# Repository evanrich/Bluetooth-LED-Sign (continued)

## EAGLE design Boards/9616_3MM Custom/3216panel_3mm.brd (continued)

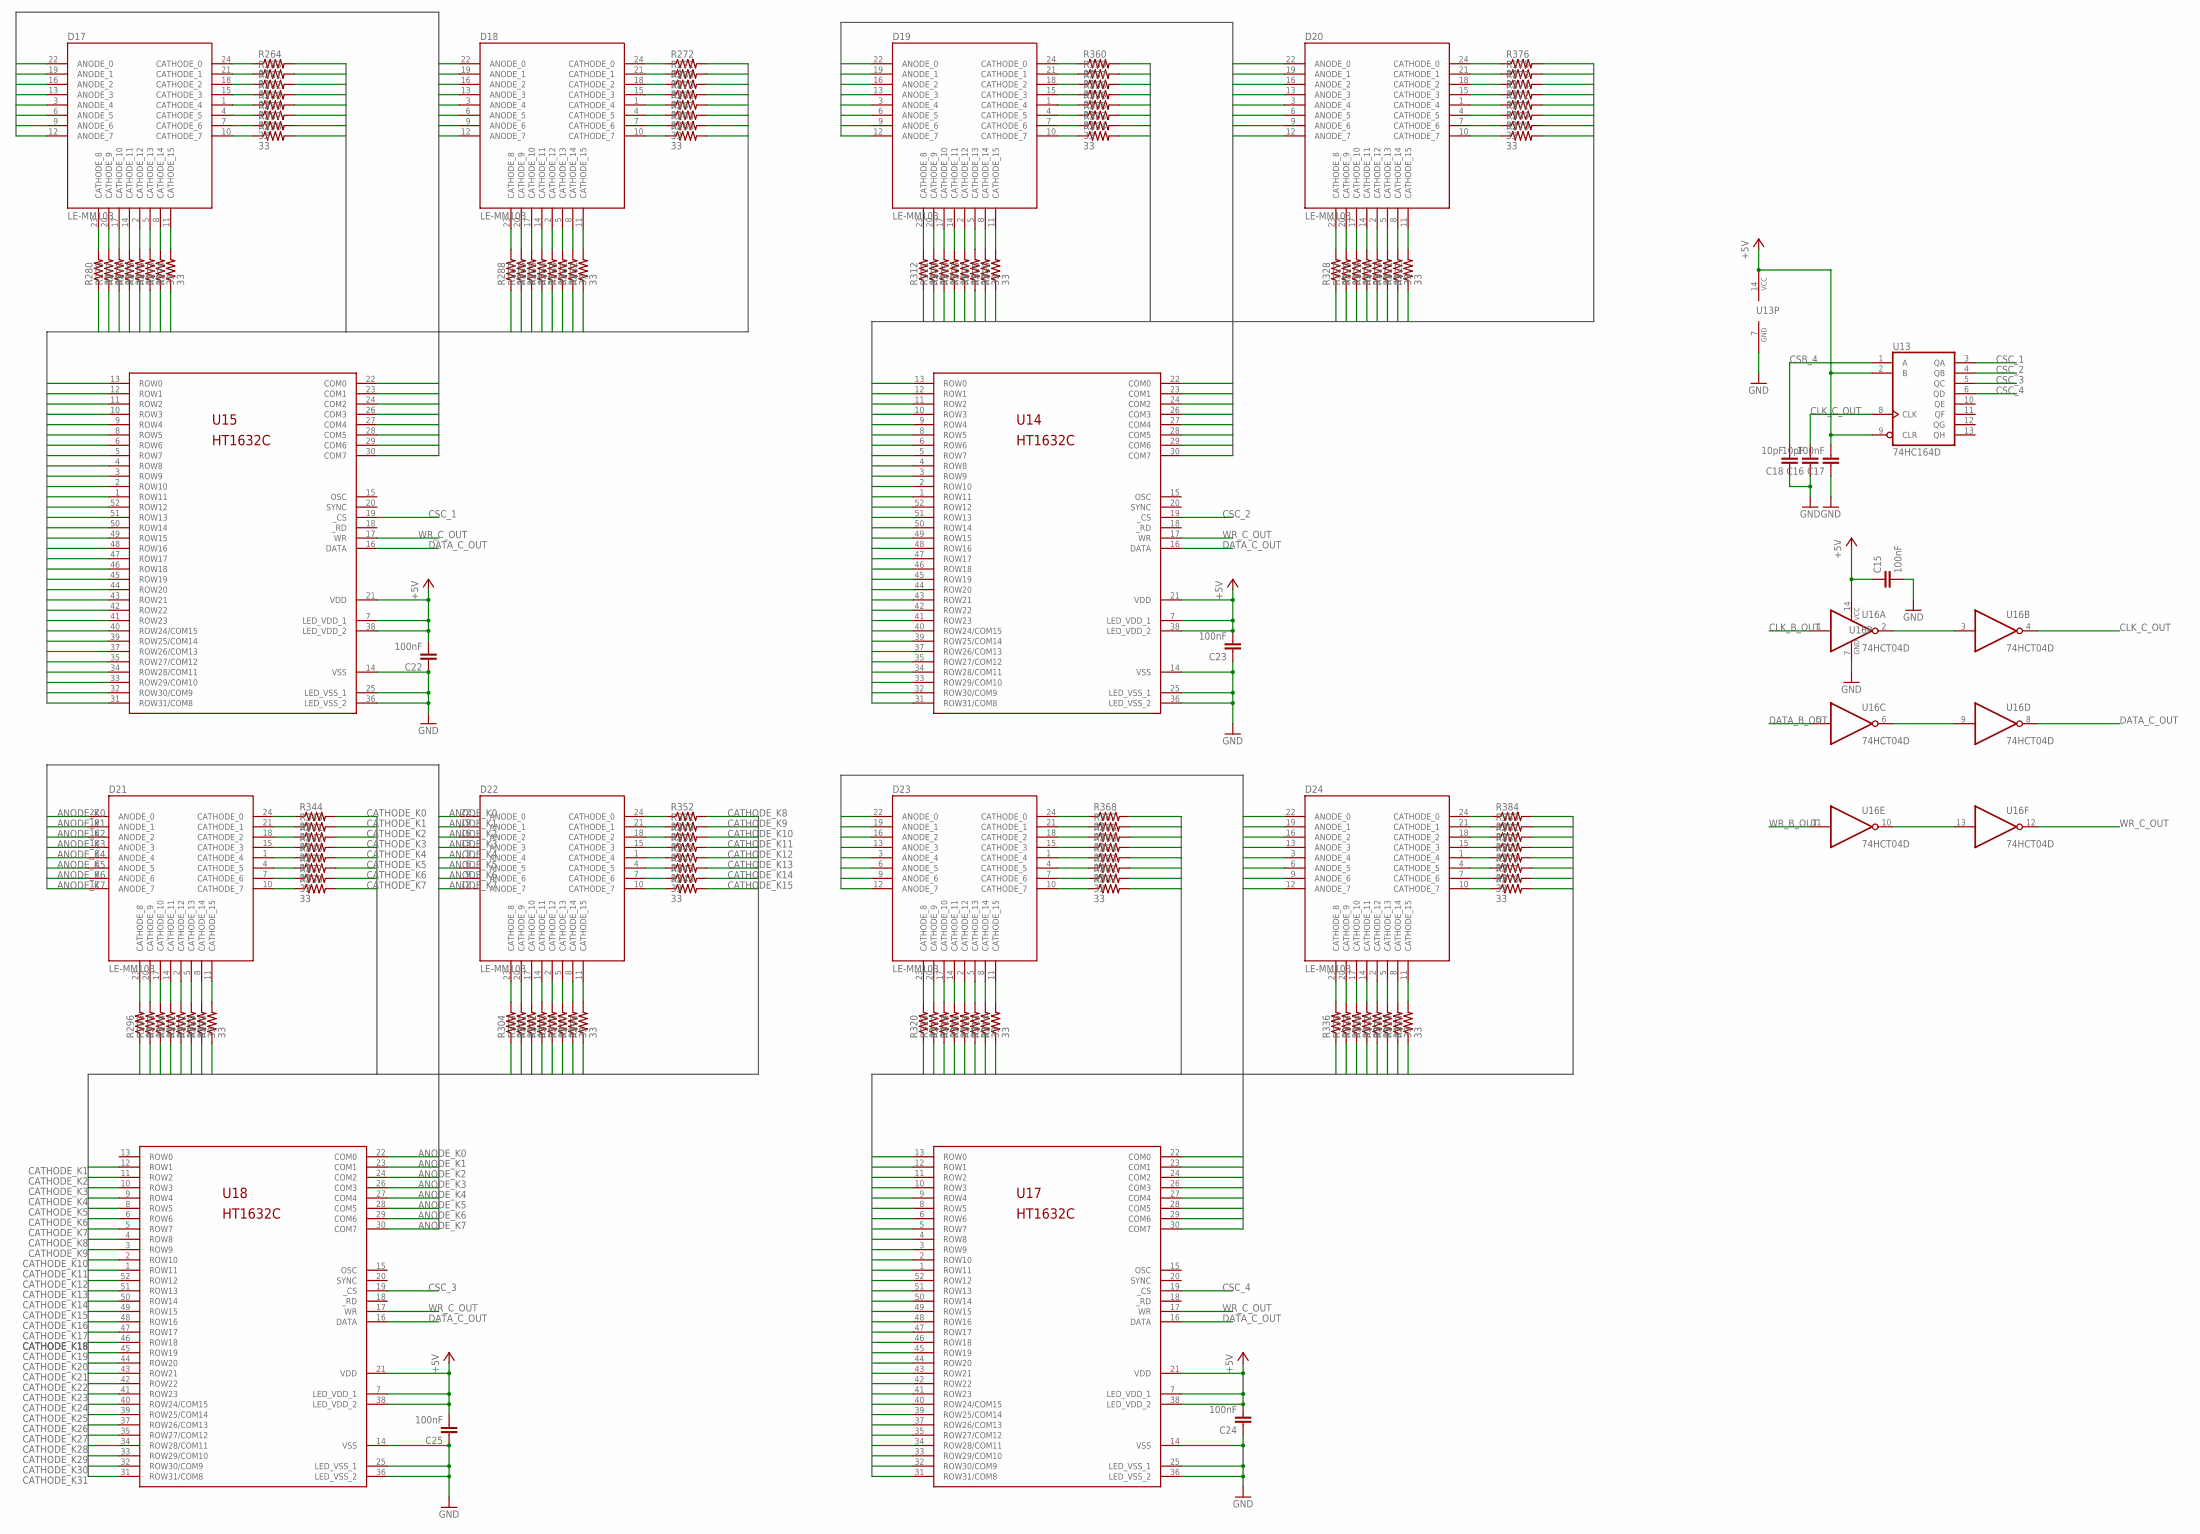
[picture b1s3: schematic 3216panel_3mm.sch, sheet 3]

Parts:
C15, C17, C22, C23, C24, C25: 100nF; 0805
C16, C18: 10pF; 0805
D17, D18, D19, D20, D21, D22, D23, D24: LE-MM103; 8X8_3MM_LED_MATRIX
R257, R258, R259, R260, R261, R262, R263, R264, R265, R266, R267, R268, R269, R270, R271, R272, R273, R274, R275, R276, R277, R278, R279, R280, R281, R282, R283, R284, R285, R286, R287, R288, R289, R290, R291, R292, R293, R294, R295, R296, R297, R298, R299, R300, R301, R302, R303, R304, R305, R306, R307, R308, R309, R310, R311, R312, R313, R314, R315, R316, R317, R318, R319, R320, R321, R322, R323, R324, R325, R326, R327, R328, R329, R330, R331, R332, R333, R334, R335, R336, R337, R338, R339, R340, R341, R342, R343, R344, R345, R346, R347, R348, R349, R350, R351, R352, R353, R354, R355, R356, R357, R358, R359, R360, R361, R362, R363, R364, R365, R366, R367, R368, R369, R370, R371, R372, R373, R374, R375, R376, R377, R378, R379, R380, R381, R382, R383, R384: 33; 0805
U13: 74HC164D; SO14
U14, U15, U17, U18: HT1632C; QFP52
U16: 74HCT04D; SO14

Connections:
+5V: C15.1, C17.2, C22.2, C23.2, C24.2, C25.2, U13.2 (B), U13.9 (CLR), U13.14 (VCC), U14.7 (LED_VDD_1), U14.21 (VDD), U14.38 (LED_VDD_2), U15.7 (LED_VDD_1), U15.21 (VDD), U15.38 (LED_VDD_2), U16.14 (VCC), U17.7 (LED_VDD_1), U17.21 (VDD), U17.38 (LED_VDD_2), U18.7 (LED_VDD_1), U18.21 (VDD), U18.38 (LED_VDD_2); also elsewhere on the board
ANODE_I0: D17.22 (ANODE_0), D18.22 (ANODE_0), U15.22 (COM0)
ANODE_I1: D17.19 (ANODE_1), D18.19 (ANODE_1), U15.23 (COM1)
ANODE_I2: D17.16 (ANODE_2), D18.16 (ANODE_2), U15.24 (COM2)
ANODE_I3: D17.13 (ANODE_3), D18.13 (ANODE_3), U15.26 (COM3)
ANODE_I4: D17.3 (ANODE_4), D18.3 (ANODE_4), U15.27 (COM4)
ANODE_I5: D17.6 (ANODE_5), D18.6 (ANODE_5), U15.28 (COM5)
ANODE_I6: D17.9 (ANODE_6), D18.9 (ANODE_6), U15.29 (COM6)
ANODE_I7: D17.12 (ANODE_7), D18.12 (ANODE_7), U15.30 (COM7)
ANODE_J0: D19.22 (ANODE_0), D20.22 (ANODE_0), U14.22 (COM0)
ANODE_J1: D19.19 (ANODE_1), D20.19 (ANODE_1), U14.23 (COM1)
ANODE_J2: D19.16 (ANODE_2), D20.16 (ANODE_2), U14.24 (COM2)
ANODE_J3: D19.13 (ANODE_3), D20.13 (ANODE_3), U14.26 (COM3)
ANODE_J4: D19.3 (ANODE_4), D20.3 (ANODE_4), U14.27 (COM4)
ANODE_J5: D19.6 (ANODE_5), D20.6 (ANODE_5), U14.28 (COM5)
ANODE_J6: D19.9 (ANODE_6), D20.9 (ANODE_6), U14.29 (COM6)
ANODE_J7: D19.12 (ANODE_7), D20.12 (ANODE_7), U14.30 (COM7)
ANODE_K0: D21.22 (ANODE_0), D22.22 (ANODE_0), U18.22 (COM0)
ANODE_K1: D21.19 (ANODE_1), D22.19 (ANODE_1), U18.23 (COM1)
ANODE_K2: D21.16 (ANODE_2), D22.16 (ANODE_2), U18.24 (COM2)
ANODE_K3: D21.13 (ANODE_3), D22.13 (ANODE_3), U18.26 (COM3)
ANODE_K4: D21.3 (ANODE_4), D22.3 (ANODE_4), U18.27 (COM4)
ANODE_K5: D21.6 (ANODE_5), D22.6 (ANODE_5), U18.28 (COM5)
ANODE_K6: D21.9 (ANODE_6), D22.9 (ANODE_6), U18.29 (COM6)
ANODE_K7: D21.12 (ANODE_7), D22.12 (ANODE_7), U18.30 (COM7)
ANODE_L0: D23.22 (ANODE_0), D24.22 (ANODE_0), U17.22 (COM0)
ANODE_L1: D23.19 (ANODE_1), D24.19 (ANODE_1), U17.23 (COM1)
ANODE_L2: D23.16 (ANODE_2), D24.16 (ANODE_2), U17.24 (COM2)
ANODE_L3: D23.13 (ANODE_3), D24.13 (ANODE_3), U17.26 (COM3)
ANODE_L4: D23.3 (ANODE_4), D24.3 (ANODE_4), U17.27 (COM4)
ANODE_L5: D23.6 (ANODE_5), D24.6 (ANODE_5), U17.28 (COM5)
ANODE_L6: D23.9 (ANODE_6), D24.9 (ANODE_6), U17.29 (COM6)
ANODE_L7: D23.12 (ANODE_7), D24.12 (ANODE_7), U17.30 (COM7)
CATHODE_I0: R264.2, U15.13 (ROW0)
CATHODE_I1: R263.2, U15.12 (ROW1)
CATHODE_I2: R261.2, U15.11 (ROW2)
CATHODE_I3: R262.2, U15.10 (ROW3)
CATHODE_I4: R260.2, U15.9 (ROW4)
CATHODE_I5: R259.2, U15.8 (ROW5)
CATHODE_I6: R257.2, U15.6 (ROW6)
CATHODE_I7: R258.2, U15.5 (ROW7)
CATHODE_I8: R272.2, U15.4 (ROW8)
CATHODE_I9: R271.2, U15.3 (ROW9)
CATHODE_I10: R269.2, U15.2 (ROW10)
CATHODE_I11: R270.2, U15.1 (ROW11)
CATHODE_I12: R268.2, U15.52 (ROW12)
CATHODE_I13: R267.2, U15.51 (ROW13)
CATHODE_I14: R265.2, U15.50 (ROW14)
CATHODE_I15: R266.2, U15.49 (ROW15)
CATHODE_I16: R280.1, U15.48 (ROW16)
CATHODE_I17: R279.1, U15.47 (ROW17)
CATHODE_I18: R277.1, U15.46 (ROW18)
CATHODE_I19: R278.1, U15.45 (ROW19)
CATHODE_I20: R276.1, U15.44 (ROW20)
CATHODE_I21: R275.1, U15.43 (ROW21)
CATHODE_I22: R273.1, U15.42 (ROW22)
CATHODE_I23: R274.1, U15.41 (ROW23)
CATHODE_I24: R288.1, U15.40 (ROW24/COM15)
CATHODE_I25: R287.1, U15.39 (ROW25/COM14)
CATHODE_I26: R285.1, U15.37 (ROW26/COM13)
CATHODE_I27: R286.1, U15.35 (ROW27/COM12)
CATHODE_I28: R284.1, U15.34 (ROW28/COM11)
CATHODE_I29: R283.1, U15.33 (ROW29/COM10)
CATHODE_I30: R281.1, U15.32 (ROW30/COM9)
CATHODE_I31: R282.1, U15.31 (ROW31/COM8)
CATHODE_J0: R360.2, U14.13 (ROW0)
CATHODE_J1: R359.2, U14.12 (ROW1)
CATHODE_J2: R357.2, U14.11 (ROW2)
CATHODE_J3: R358.2, U14.10 (ROW3)
CATHODE_J4: R356.2, U14.9 (ROW4)
CATHODE_J5: R355.2, U14.8 (ROW5)
CATHODE_J6: R353.2, U14.6 (ROW6)
CATHODE_J7: R354.2, U14.5 (ROW7)
CATHODE_J8: R376.2, U14.4 (ROW8)
CATHODE_J9: R375.2, U14.3 (ROW9)
CATHODE_J10: R373.2, U14.2 (ROW10)
CATHODE_J11: R374.2, U14.1 (ROW11)
CATHODE_J12: R372.2, U14.52 (ROW12)
CATHODE_J13: R371.2, U14.51 (ROW13)
CATHODE_J14: R369.2, U14.50 (ROW14)
CATHODE_J15: R370.2, U14.49 (ROW15)
CATHODE_J16: R312.1, U14.48 (ROW16)
CATHODE_J17: R311.1, U14.47 (ROW17)
CATHODE_J18: R309.1, U14.46 (ROW18)
CATHODE_J19: R310.1, U14.45 (ROW19)
CATHODE_J20: R308.1, U14.44 (ROW20)
CATHODE_J21: R307.1, U14.43 (ROW21)
CATHODE_J22: R305.1, U14.42 (ROW22)
CATHODE_J23: R306.1, U14.41 (ROW23)
CATHODE_J24: R328.1, U14.40 (ROW24/COM15)
CATHODE_J25: R327.1, U14.39 (ROW25/COM14)
CATHODE_J26: R325.1, U14.37 (ROW26/COM13)
CATHODE_J27: R326.1, U14.35 (ROW27/COM12)
CATHODE_J28: R324.1, U14.34 (ROW28/COM11)
CATHODE_J29: R323.1, U14.33 (ROW29/COM10)
CATHODE_J30: R321.1, U14.32 (ROW30/COM9)
CATHODE_J31: R322.1, U14.31 (ROW31/COM8)
CATHODE_K0: R344.2
CATHODE_K1: R343.2, U18.12 (ROW1)
CATHODE_K2: R341.2, U18.11 (ROW2)
CATHODE_K3: R342.2, U18.10 (ROW3)
CATHODE_K4: R340.2, U18.9 (ROW4)
CATHODE_K5: R339.2, U18.8 (ROW5)
CATHODE_K6: R337.2, U18.6 (ROW6)
CATHODE_K7: R338.2, U18.5 (ROW7)
CATHODE_K8: R352.2, U18.4 (ROW8)
CATHODE_K9: R351.2, U18.3 (ROW9)
CATHODE_K10: R349.2, U18.2 (ROW10)
CATHODE_K11: R350.2, U18.1 (ROW11)
CATHODE_K12: R348.2, U18.52 (ROW12)
CATHODE_K13: R347.2, U18.51 (ROW13)
CATHODE_K14: R345.2, U18.50 (ROW14)
CATHODE_K15: R346.2, U18.49 (ROW15)
CATHODE_K16: R296.1, U18.48 (ROW16)
CATHODE_K17: R295.1, U18.47 (ROW17)
CATHODE_K18: R293.1, U18.46 (ROW18)
CATHODE_K19: R294.1, U18.45 (ROW19)
CATHODE_K20: R292.1, U18.44 (ROW20)
CATHODE_K21: R291.1, U18.43 (ROW21)
CATHODE_K22: R289.1, U18.42 (ROW22)
CATHODE_K23: R290.1, U18.41 (ROW23)
CATHODE_K24: R304.1, U18.40 (ROW24/COM15)
CATHODE_K25: R303.1, U18.39 (ROW25/COM14)
CATHODE_K26: R301.1, U18.37 (ROW26/COM13)
CATHODE_K27: R302.1, U18.35 (ROW27/COM12)
CATHODE_K28: R300.1, U18.34 (ROW28/COM11)
CATHODE_K29: R299.1, U18.33 (ROW29/COM10)
CATHODE_K30: R297.1, U18.32 (ROW30/COM9)
CATHODE_K31: R298.1, U18.31 (ROW31/COM8)
CATHODE_L0: R368.2, U17.13 (ROW0)
CATHODE_L1: R367.2, U17.12 (ROW1)
CATHODE_L2: R365.2, U17.11 (ROW2)
CATHODE_L3: R366.2, U17.10 (ROW3)
CATHODE_L4: R364.2, U17.9 (ROW4)
CATHODE_L5: R363.2, U17.8 (ROW5)
CATHODE_L6: R361.2, U17.6 (ROW6)
CATHODE_L7: R362.2, U17.5 (ROW7)
CATHODE_L8: R384.2, U17.4 (ROW8)
CATHODE_L9: R383.2, U17.3 (ROW9)
CATHODE_L10: R381.2, U17.2 (ROW10)
CATHODE_L11: R382.2, U17.1 (ROW11)
CATHODE_L12: R380.2, U17.52 (ROW12)
CATHODE_L13: R379.2, U17.51 (ROW13)
CATHODE_L14: R377.2, U17.50 (ROW14)
CATHODE_L15: R378.2, U17.49 (ROW15)
CATHODE_L16: R320.1, U17.48 (ROW16)
CATHODE_L17: R319.1, U17.47 (ROW17)
CATHODE_L18: R317.1, U17.46 (ROW18)
CATHODE_L19: R318.1, U17.45 (ROW19)
CATHODE_L20: R316.1, U17.44 (ROW20)
CATHODE_L21: R315.1, U17.43 (ROW21)
CATHODE_L22: R313.1, U17.42 (ROW22)
CATHODE_L23: R314.1, U17.41 (ROW23)
CATHODE_L24: R336.1, U17.40 (ROW24/COM15)
CATHODE_L25: R335.1, U17.39 (ROW25/COM14)
CATHODE_L26: R333.1, U17.37 (ROW26/COM13)
CATHODE_L27: R334.1, U17.35 (ROW27/COM12)
CATHODE_L28: R332.1, U17.34 (ROW28/COM11)
CATHODE_L29: R331.1, U17.33 (ROW29/COM10)
CATHODE_L30: R329.1, U17.32 (ROW30/COM9)
CATHODE_L31: R330.1, U17.31 (ROW31/COM8)
CLK_B_OUT: U16.1 (I); also elsewhere on the board
CLK_C_OUT: C16.2, U13.8 (CLK), U16.4 (O)
CSB_4: C18.2, U13.1 (A); also elsewhere on the board
CSC_1: U13.3 (QA), U15.19 (_CS)
CSC_2: U13.4 (QB), U14.19 (_CS)
CSC_3: U13.5 (QC), U18.19 (_CS)
CSC_4: U13.6 (QD), U17.19 (_CS)
DATA_B_OUT: U16.5 (I); also elsewhere on the board
DATA_C_OUT: U14.16 (DATA), U15.16 (DATA), U16.8 (O), U17.16 (DATA), U18.16 (DATA)
GND: C15.2, C16.1, C17.1, C18.1, C22.1, C23.1, C24.1, C25.1, U13.7 (GND), U14.14 (VSS), U14.25 (LED_VSS_1), U14.36 (LED_VSS_2), U15.14 (VSS), U15.25 (LED_VSS_1), U15.36 (LED_VSS_2), U16.7 (GND), U17.14 (VSS), U17.25 (LED_VSS_1), U17.36 (LED_VSS_2), U18.14 (VSS), U18.25 (LED_VSS_1), U18.36 (LED_VSS_2); also elsewhere on the board
unnamed: U16.2 (O), U16.3 (I)
unnamed: U16.6 (O), U16.9 (I)
unnamed: U16.10 (O), U16.13 (I)
unnamed: D22.10 (CATHODE_7), R346.1
unnamed: D22.7 (CATHODE_6), R345.1
unnamed: D22.4 (CATHODE_5), R347.1
unnamed: D22.1 (CATHODE_4), R348.1
unnamed: D22.15 (CATHODE_3), R350.1
unnamed: D22.18 (CATHODE_2), R349.1
unnamed: D22.21 (CATHODE_1), R351.1
unnamed: D22.24 (CATHODE_0), R352.1
unnamed: D20.7 (CATHODE_6), R369.1
unnamed: D20.10 (CATHODE_7), R370.1
unnamed: D20.4 (CATHODE_5), R371.1
unnamed: D20.1 (CATHODE_4), R372.1
unnamed: D20.18 (CATHODE_2), R373.1
unnamed: D20.15 (CATHODE_3), R374.1
unnamed: D20.21 (CATHODE_1), R375.1
unnamed: D20.24 (CATHODE_0), R376.1
unnamed: D20.8 (CATHODE_14), R321.2
unnamed: D20.11 (CATHODE_15), R322.2
unnamed: D20.5 (CATHODE_13), R323.2
unnamed: D20.2 (CATHODE_12), R324.2
unnamed: D20.17 (CATHODE_10), R325.2
unnamed: D20.14 (CATHODE_11), R326.2
unnamed: D20.20 (CATHODE_9), R327.2
unnamed: D20.23 (CATHODE_8), R328.2
unnamed: D19.8 (CATHODE_14), R305.2
unnamed: D19.11 (CATHODE_15), R306.2
unnamed: D19.5 (CATHODE_13), R307.2
unnamed: D19.2 (CATHODE_12), R308.2
unnamed: D19.17 (CATHODE_10), R309.2
unnamed: D19.14 (CATHODE_11), R310.2
unnamed: D19.20 (CATHODE_9), R311.2
unnamed: D19.23 (CATHODE_8), R312.2
unnamed: D19.7 (CATHODE_6), R353.1
unnamed: D19.10 (CATHODE_7), R354.1
unnamed: D19.4 (CATHODE_5), R355.1
unnamed: D19.1 (CATHODE_4), R356.1
unnamed: D19.18 (CATHODE_2), R357.1
unnamed: D19.15 (CATHODE_3), R358.1
unnamed: D19.21 (CATHODE_1), R359.1
unnamed: D19.24 (CATHODE_0), R360.1
unnamed: D18.7 (CATHODE_6), R265.1
unnamed: D18.10 (CATHODE_7), R266.1
unnamed: D18.4 (CATHODE_5), R267.1
unnamed: D18.1 (CATHODE_4), R268.1
unnamed: D18.18 (CATHODE_2), R269.1
unnamed: D18.15 (CATHODE_3), R270.1
unnamed: D18.21 (CATHODE_1), R271.1
unnamed: D18.24 (CATHODE_0), R272.1
unnamed: D18.8 (CATHODE_14), R281.2
unnamed: D18.11 (CATHODE_15), R282.2
unnamed: D18.5 (CATHODE_13), R283.2
unnamed: D18.2 (CATHODE_12), R284.2
unnamed: D18.17 (CATHODE_10), R285.2
unnamed: D18.14 (CATHODE_11), R286.2
unnamed: D18.20 (CATHODE_9), R287.2
unnamed: D18.23 (CATHODE_8), R288.2
unnamed: D17.7 (CATHODE_6), R257.1
unnamed: D17.10 (CATHODE_7), R258.1
unnamed: D17.4 (CATHODE_5), R259.1
unnamed: D17.1 (CATHODE_4), R260.1
unnamed: D17.18 (CATHODE_2), R261.1
unnamed: D17.15 (CATHODE_3), R262.1
unnamed: D17.21 (CATHODE_1), R263.1
unnamed: D17.24 (CATHODE_0), R264.1
unnamed: D17.8 (CATHODE_14), R273.2
unnamed: D17.11 (CATHODE_15), R274.2
unnamed: D17.5 (CATHODE_13), R275.2
unnamed: D17.2 (CATHODE_12), R276.2
unnamed: D17.17 (CATHODE_10), R277.2
unnamed: D17.14 (CATHODE_11), R278.2
unnamed: D17.20 (CATHODE_9), R279.2
unnamed: D17.23 (CATHODE_8), R280.2
unnamed: D21.7 (CATHODE_6), R337.1
unnamed: D21.10 (CATHODE_7), R338.1
unnamed: D21.4 (CATHODE_5), R339.1
unnamed: D21.1 (CATHODE_4), R340.1
unnamed: D21.18 (CATHODE_2), R341.1
unnamed: D21.15 (CATHODE_3), R342.1
unnamed: D21.21 (CATHODE_1), R343.1
unnamed: D21.24 (CATHODE_0), R344.1
unnamed: D21.8 (CATHODE_14), R289.2
unnamed: D21.11 (CATHODE_15), R290.2
unnamed: D21.5 (CATHODE_13), R291.2
unnamed: D21.2 (CATHODE_12), R292.2
unnamed: D21.17 (CATHODE_10), R293.2
unnamed: D21.14 (CATHODE_11), R294.2
unnamed: D21.20 (CATHODE_9), R295.2
unnamed: D21.23 (CATHODE_8), R296.2
unnamed: D22.8 (CATHODE_14), R297.2
unnamed: D22.11 (CATHODE_15), R298.2
unnamed: D22.5 (CATHODE_13), R299.2
unnamed: D22.2 (CATHODE_12), R300.2
unnamed: D22.17 (CATHODE_10), R301.2
unnamed: D22.14 (CATHODE_11), R302.2
unnamed: D22.20 (CATHODE_9), R303.2
unnamed: D22.23 (CATHODE_8), R304.2
unnamed: D23.8 (CATHODE_14), R313.2
unnamed: D23.11 (CATHODE_15), R314.2
unnamed: D23.5 (CATHODE_13), R315.2
unnamed: D23.2 (CATHODE_12), R316.2
unnamed: D23.17 (CATHODE_10), R317.2
unnamed: D23.14 (CATHODE_11), R318.2
unnamed: D23.20 (CATHODE_9), R319.2
unnamed: D23.23 (CATHODE_8), R320.2
unnamed: D23.7 (CATHODE_6), R361.1
unnamed: D23.10 (CATHODE_7), R362.1
unnamed: D23.4 (CATHODE_5), R363.1
unnamed: D23.1 (CATHODE_4), R364.1
unnamed: D23.18 (CATHODE_2), R365.1
unnamed: D23.15 (CATHODE_3), R366.1
unnamed: D23.21 (CATHODE_1), R367.1
unnamed: D23.24 (CATHODE_0), R368.1
unnamed: D24.7 (CATHODE_6), R377.1
unnamed: D24.10 (CATHODE_7), R378.1
unnamed: D24.4 (CATHODE_5), R379.1
unnamed: D24.1 (CATHODE_4), R380.1
unnamed: D24.18 (CATHODE_2), R381.1
unnamed: D24.15 (CATHODE_3), R382.1
unnamed: D24.21 (CATHODE_1), R383.1
unnamed: D24.24 (CATHODE_0), R384.1
unnamed: D24.8 (CATHODE_14), R329.2
unnamed: D24.11 (CATHODE_15), R330.2
unnamed: D24.5 (CATHODE_13), R331.2
unnamed: D24.2 (CATHODE_12), R332.2
unnamed: D24.17 (CATHODE_10), R333.2
unnamed: D24.14 (CATHODE_11), R334.2
unnamed: D24.20 (CATHODE_9), R335.2
unnamed: D24.23 (CATHODE_8), R336.2
WR_B_OUT: U16.11 (I); also elsewhere on the board
WR_C_OUT: U14.17 (WR), U15.17 (WR), U16.12 (O), U17.17 (WR), U18.17 (WR)

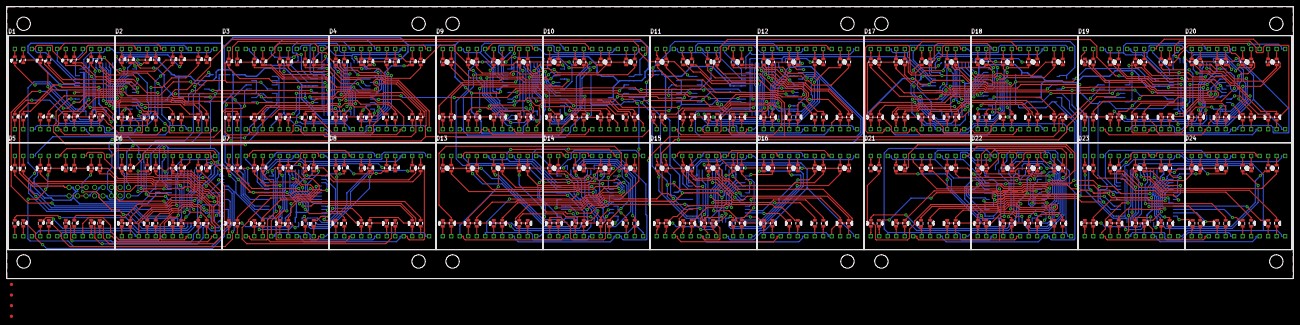
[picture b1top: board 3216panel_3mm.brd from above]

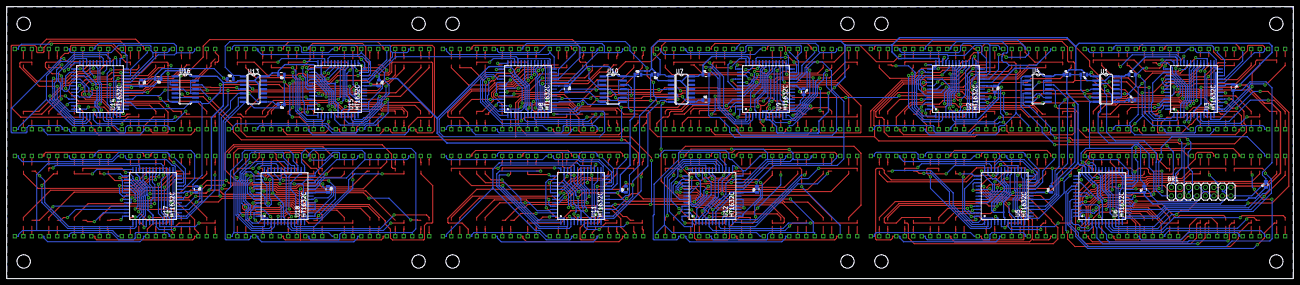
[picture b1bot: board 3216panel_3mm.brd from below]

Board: 2 copper layers, 384.8 x 81.3 mm, 456 parts (44 on the bottom side), 899 nets.

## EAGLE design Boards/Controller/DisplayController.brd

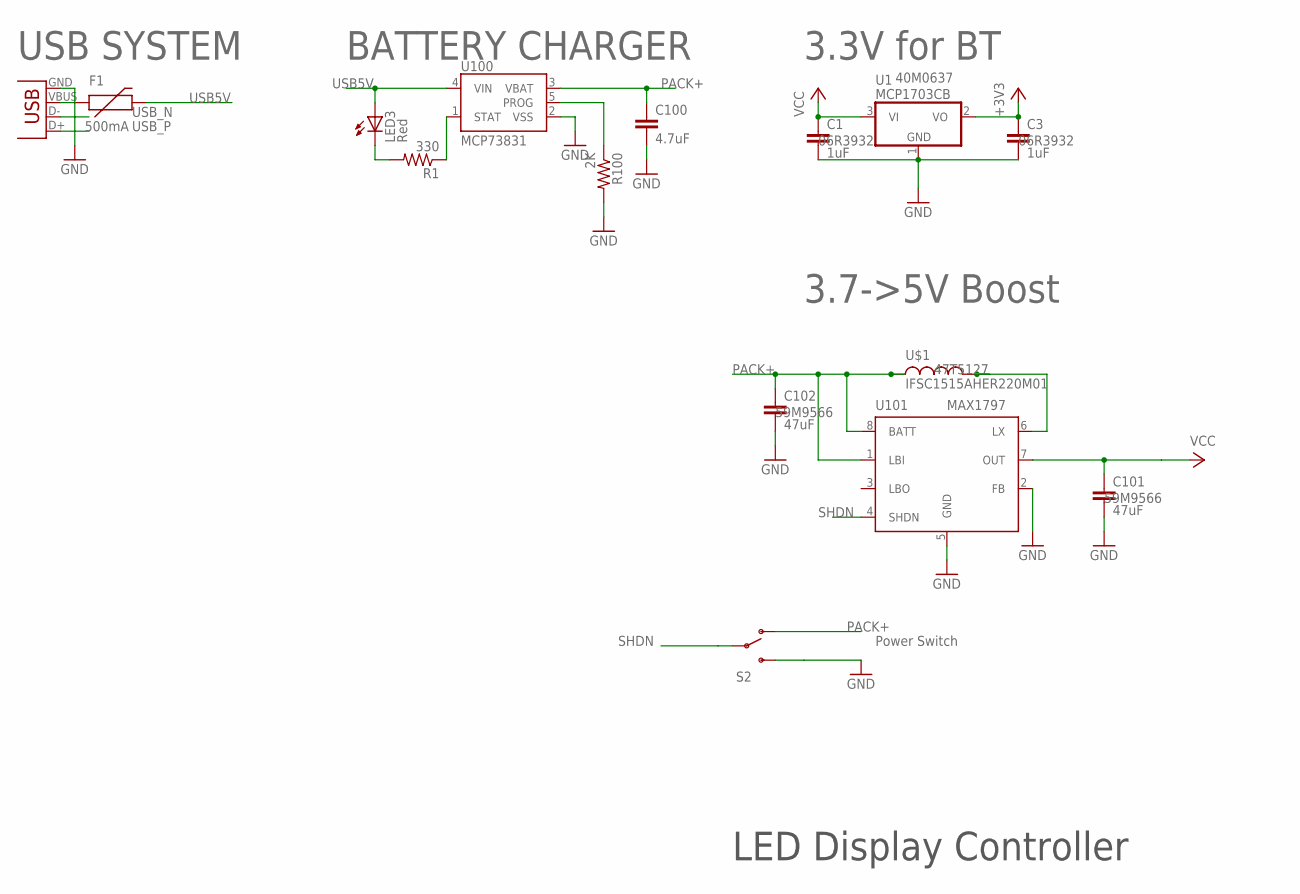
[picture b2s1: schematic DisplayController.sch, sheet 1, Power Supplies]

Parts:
C1, C3: 1uF; 0805
C100: 4.7uF; 0603-CAP
C101, C102: 47uF; 1206
F1: 500mA; PTC-1206
J1: USB0001LF; 10104110-0001LF
LED3: Red; LED-0603
R1: 330; 0603-RES
R100: 2K; 0805
S2: SWITCH-SPDT-SMD-A; SWITCH-SPST-SMD-A
U1: MCP1703CB; SOT23
U100: MCP73831; SOT23-5
U101: MAX1797; UMAX8
U$1: IFSC1515AHER220M01; IFSC

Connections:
+3V3: C3.1, U1.2 (VO); also elsewhere on the board
GND: C1.2, C3.2, C100.2, C101.2, C102.2, J1.GND, R100.2, S2.3 (S), U1.1 (GND), U100.2 (VSS), U101.2 (FB), U101.5 (GND); also elsewhere on the board
unnamed: F1.1, J1.VBUS
unnamed: R1.1, U100.1 (STAT)
unnamed: LED3.C, R1.2
unnamed: R100.1, U100.5 (PROG)
unnamed: U101.6 (LX), U$1.2
PACK+: C100.1, C102.1, S2.1 (O), U100.3 (VBAT), U101.1 (LBI), U101.8 (BATT), U$1.1; also elsewhere on the board
SHDN: S2.2, U101.4 (SHDN)
USB5V: F1.2, LED3.A, U100.4 (VIN); also elsewhere on the board
USB_N: J1.D-; also elsewhere on the board
USB_P: J1.D+; also elsewhere on the board
VCC: C1.1, C101.1, U1.3 (VI), U101.7 (OUT); also elsewhere on the board

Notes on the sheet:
BATTERY CHARGER
USB SYSTEM
3.3V for BT
Power Switch
LED Display Controller
3.7->5V Boost

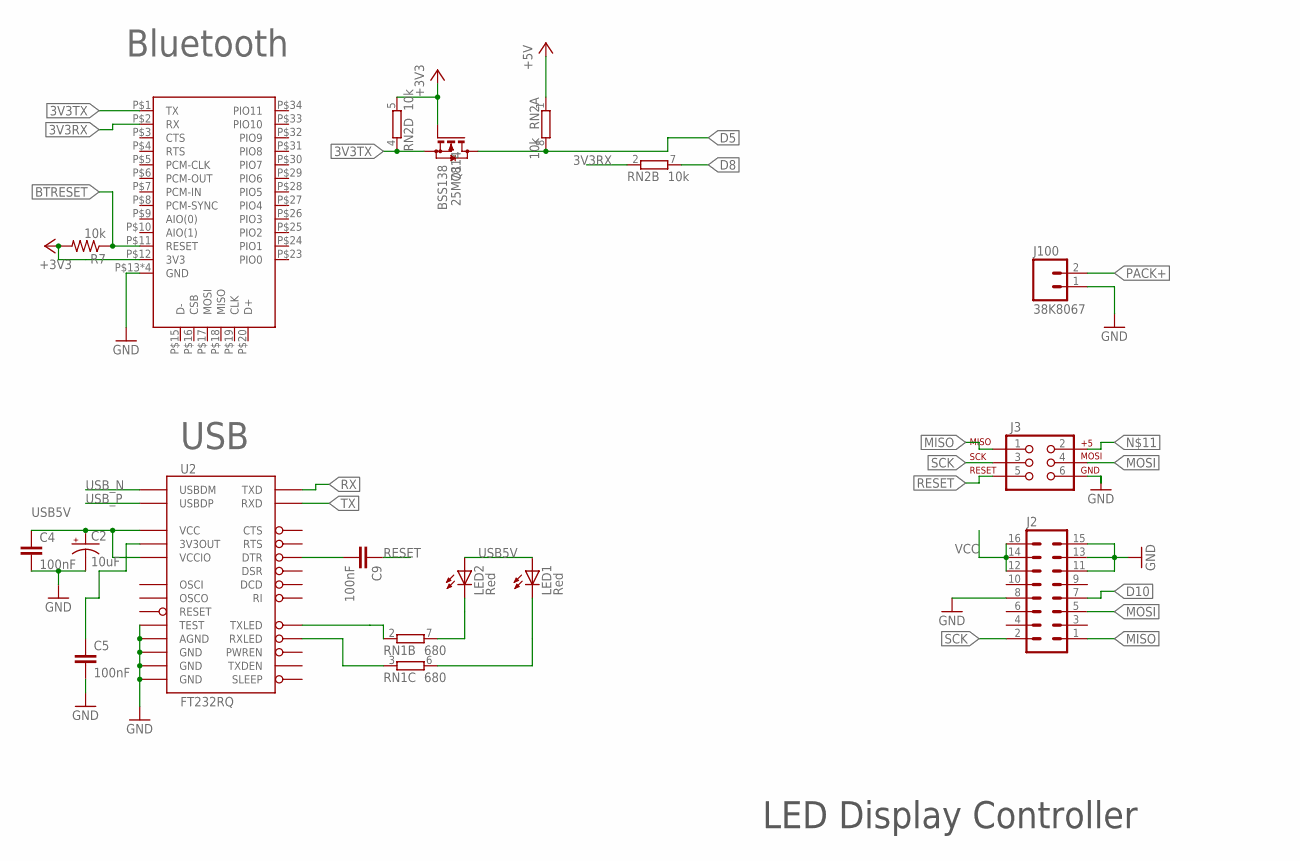
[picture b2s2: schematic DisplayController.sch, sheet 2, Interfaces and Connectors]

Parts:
C2: 10uF; EIA3216
C4, C5, C9: 100nF; 0603-CAP
J2: MA08-2
J3: AVR_SPI_PRG_62X3_LOCK; 2X3_LOCK
J100: 38K8067; JST-2-SMD
LED1, LED2: Red; LED-0603
Q1: BSS138; SOT23
R7: 10k; 0603-RES
RN1: 680; EXB38V
RN2: 10k; EXB38V
U2: FT232RQ; QFN-32
U$2: DX_BT_MODULE; DXBLUETOOTHMODULE

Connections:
3V3RX: RN2.2 (1), U$2.P$2 (RX)
3V3TX: Q1.2 (S), RN2.4 (1), U$2.P$1 (TX)
+3V3: Q1.1 (G), R7.2, RN2.5 (2), U$2.P$12 (3V3); also elsewhere on the board
BTRESET: R7.1, U$2.P$11 (RESET); also elsewhere on the board
D5: Q1.3 (D), RN2.8 (2); also elsewhere on the board
D8: RN2.7 (2); also elsewhere on the board
D10: J2.7; also elsewhere on the board
GND: C2.C (-), C4.2, C5.2, J2.8, J2.11, J2.13, J2.15, J3.6, J100.1, U2.4 (GND), U2.17 (GND), U2.20 (GND), U2.24 (AGND), U2.26 (TEST), U$2.P$13 (GND), U$2.P$14 (GND), U$2.P$21 (GND), U$2.P$22 (GND); also elsewhere on the board
MISO: J2.1, J3.1; also elsewhere on the board
MOSI: J2.5, J3.4; also elsewhere on the board
unnamed: RN1.2 (1), U2.22 (TXLED)
unnamed: RN1.3 (1), U2.21 (RXLED)
unnamed: LED1.C, RN1.6 (2)
unnamed: LED2.C, RN1.7 (2)
unnamed: C9.2, U2.31 (DTR)
unnamed: C5.1, U2.16 (3V3OUT)
PACK+: J100.2; also elsewhere on the board
RESET: C9.1, J3.5; also elsewhere on the board
RX: U2.30 (TXD); also elsewhere on the board
SCK: J2.2, J3.3; also elsewhere on the board
TX: U2.2 (RXD); also elsewhere on the board
USB5V: C2.A (+), C4.1, LED1.A, LED2.A, U2.1 (VCCIO), U2.19 (VCC); also elsewhere on the board
USB_N: U2.15 (USBDM); also elsewhere on the board
USB_P: U2.14 (USBDP); also elsewhere on the board
VCC: J2.12, J2.14, J2.16, RN2.1; also elsewhere on the board

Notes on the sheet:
Bluetooth
USB
LED Display Controller

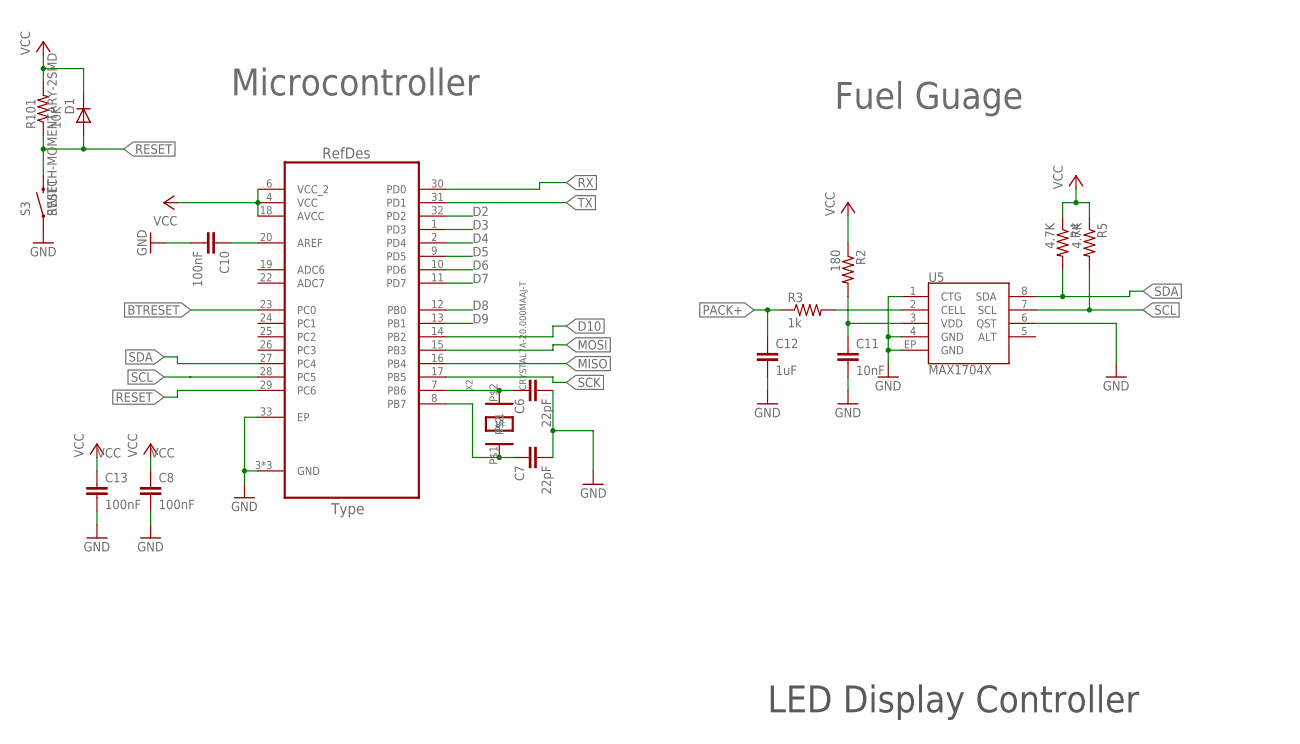
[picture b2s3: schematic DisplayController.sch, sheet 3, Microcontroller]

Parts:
C6, C7: 22pF; 0603-CAP
C8, C13: 100nF; 0603-CAP
C10: 100nF; 0805
C11: 10nF; 0603-CAP
C12: 1uF; 0603-CAP
D1: LEDSML1206; SML1206
R2: 180; 0603-RES
R3: 1k; 0603-RES
R4, R5: 4.7K; 0603-RES
R101: 10K; 0805
S3: SWITCH-MOMENTARY-2SMD; TACTILE_SWITCH_SMD
U3: ATMEGA328P-MU; QFN50P500X500X100-33N
U5: MAX1704X; TDFN-8
X2: CRYSTAL7A-20.000MAAJ-T; 7A

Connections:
BTRESET: U3.23 (PC0); also elsewhere on the board
D2: U3.32 (PD2)
D3: U3.1 (PD3)
D4: U3.2 (PD4)
D5: U3.9 (PD5); also elsewhere on the board
D6: U3.10 (PD6)
D7: U3.11 (PD7)
D8: U3.12 (PB0); also elsewhere on the board
D9: U3.13 (PB1)
D10: U3.14 (PB2); also elsewhere on the board
GND: C6.2, C7.2, C8.2, C10.2, C11.2, C12.2, C13.2, S3.1, U3.3 (GND), U3.5 (GND), U3.21 (GND), U3.33 (EP), U5.1 (CTG), U5.4 (GND), U5.6 (QST), U5.EP (GND); also elsewhere on the board
MISO: U3.16 (PB4); also elsewhere on the board
MOSI: U3.15 (PB3); also elsewhere on the board
unnamed: C10.1, U3.20 (AREF)
unnamed: C6.1, U3.7 (PB6), X2.P$2
unnamed: C7.1, U3.8 (PB7), X2.P$1
unnamed: C11.1, R2.2, U5.3 (VDD)
unnamed: R3.2, U5.2 (CELL)
PACK+: C12.1, R3.1; also elsewhere on the board
RESET: D1.A, R101.1, S3.3 (2), U3.29 (PC6); also elsewhere on the board
RX: U3.30 (PD0); also elsewhere on the board
SCK: U3.17 (PB5); also elsewhere on the board
SCL: R5.2, U3.28 (PC5), U5.7 (SCL)
SDA: R4.2, U3.27 (PC4), U5.8 (SDA)
TX: U3.31 (PD1); also elsewhere on the board
VCC: C8.1, C13.1, D1.C, R2.1, R4.1, R5.1, R101.2, U3.4 (VCC), U3.6 (VCC_2), U3.18 (AVCC); also elsewhere on the board

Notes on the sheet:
RESET
Microcontroller
Fuel Guage
LED Display Controller

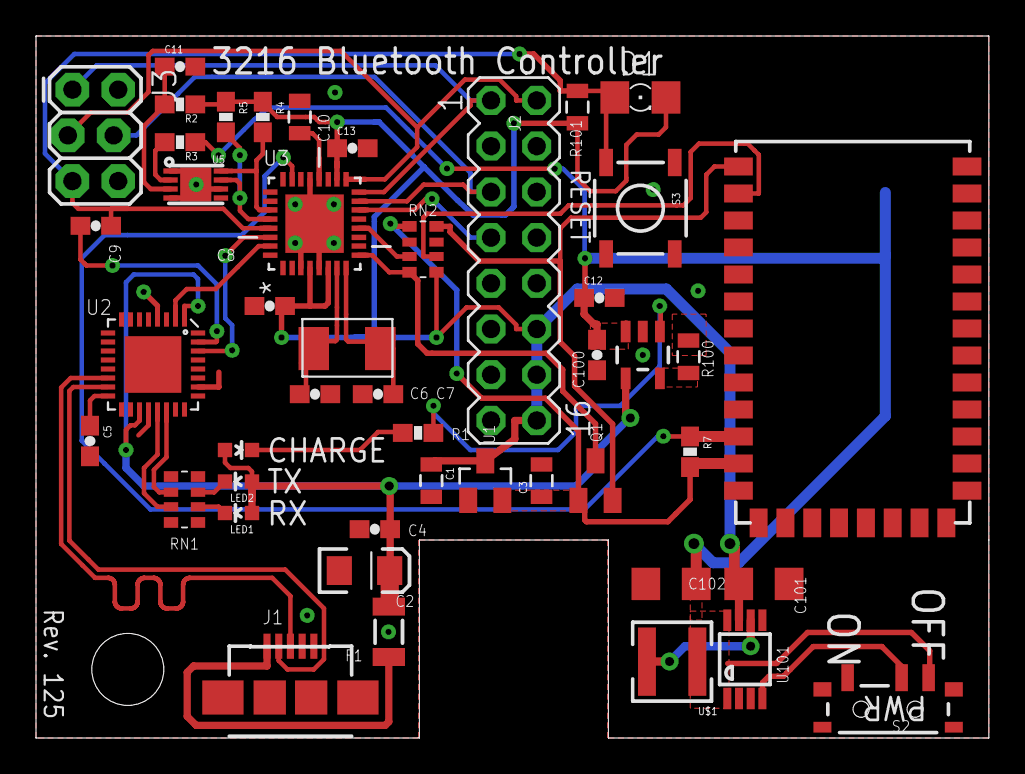
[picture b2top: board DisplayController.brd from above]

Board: 2 copper layers, 52.9 x 39.0 mm, 47 parts (1 on the bottom side), 38 nets.

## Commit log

2012-01-19 Initial import from SVN to Git of Android controller Initial import from SVN to Git of .NET controller
2012-01-19 reverted back to old chat code, was testing screen rotation, changes didn't fix anything.
2012-01-19 Included Credits in README First import of Arduino Library and 1.0 code Added first batch of data sheets
2012-01-19 moved 1.0 code into its own folder Added 0023 (old) code
2012-01-20 Added Controller BoardSchematic
2012-01-20 Added CC license info
2012-01-20 Rename README
2012-01-20 renamed readme back
2012-01-20 fixed typo in Features
2012-01-20 Created gh-pages branch via GitHub
2012-01-21 Added Libraries used for parts, My own custom, and current Sparkfun library. Libraries are EAGLE 6 format, and will not work in Eagle 5.
2012-01-21 Added Custom 96x16 panel display board (Board is still being routed)
2012-01-25 Increased +5V trace width to 0.6096mm cleaned up traces removed 3 vias changed to eagle 6.1.0
2012-01-25 added board images and images folder
2012-02-01 Finished routing board (for Sierra Circuits/PCBCart.com specs)
2012-02-01 updated layout for controller.
2012-02-02 Added various logic, capacitor, and resistor datasheets
2012-02-02 added fiducial marks increased 5V supply to 16mil
2012-02-03 Added Gerbers for 96x16 Board
2012-02-03 Added HT1632C datasheets
2012-02-03 Added Thermistor to determine board temperature Cleaned up thermal vias and traces under ICs
2012-02-03 Added 8x2 Header for Display board
2012-02-03 Removed extra ground via from under crystal
2012-02-04 cleaned up controller traces replaced power switch with new part from sparkfun (deprecated old switch) removed thermistor (nice to have but not really needed for now)
2012-02-07 updated layout
2012-02-07 moved Power supplies to top side cleaned up traces moved reset switch near display connector Added various Newark part numbers to board parts
2012-02-07 Added android screenshot (default view) Fixed size on controllerboard.png
2012-02-07 changed controller dimensions (shrunk board width by 0.05")
2012-02-07 Updated documentation to-do, BOM nearly finalized.
2012-02-07 added Rev Number (SVN 123) cosmetics
2012-02-08 Fixed Screen Rotation so Service does not get destroyed on rotation.
2012-02-08 removed screen rotation known issue, fixed in code
2012-02-08 removed fixed Known issues
2012-02-08 Added Switch datasheets (a few alternates added that are drop in replacements) Added more Newark.com PN's to various parts
2012-02-08 removed stray ground symbol that was a copy never used.
2012-02-08 added more android screenshots
2012-02-08 resized images to 240x400 (down from 480x800)
2012-02-10 Added Gerbers
2012-02-10 Fixed bottom ground plane being .2mm above outline Cleaned up traces a bit Added 100uF cap to top power pin of atmega328p (all power pins now have a cap) Added 10k resistor to BT module reset line (t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
2012-02-10 Adjusted Frame to fill whole schematic, and changed layer
2012-02-10 Added more xref labels to connections
2012-02-10 Added scanned front and back of 9616 board
2012-02-12 connected bluetooth reset to microcontroller
2012-02-12 Added notice about matrix boards needing to be common cathode (ones sourced were anode)
2012-02-13 removed 1K resistor from TX + RX between ATMega328p and FT232RQ, not needed as nothing else is connected to these pins.
2012-02-13 Added Switching diode to reset line on atmega328 (per arduino forums/Uno R3 design)
2012-02-14 Added Capacitor and New reset switch datashhets
2012-02-14 updated part info
2012-02-15 Scanned new images for front and back (1/3 populated board)
2012-02-15 cropped space off board bottom
2012-02-16 Added known/unknown working section to identify what has been tested and confirmed working, and what has yet to be tested (although has been tested in pieces already, just not as a whole)
2012-02-17 updated library from libraries source
2012-02-17 removed copied folder
2012-02-17 removed google code folder
2012-02-17 updated files in 1.0 library (pulled from library source)
2012-02-18 added landscape android image
2012-03-02 added front and back scans of controller board
2012-03-02 Added Updates section
2012-03-09 added notice about missing trace for 2nd row of 3rd and 4th top displays. added stencil info to readme
2012-03-09 added missing connection between pins 19 on LED matrix and pin 23 on controller for top right 2 displays
2012-03-09 fixed missing connection on pin 19 of 3rd/4th top displays on left side of Boards/9616_3MM Custom/3216panel_3mm.brd
2012-03-10 Removed Incorrect LED Matrix Datasheet, replaced with correct one (common cathode)
2012-03-10 Moved Data sheets into folders by Project (Display and Controller) to help anyone know which belongs to which
2012-03-10 Added "How you can help" section
2012-03-13 update to most recent version of library
2012-03-13 added "&" in front of the port to comply with the updated 1.0 library
2012-03-14 added note to updates that 9616board only works 1/3. Need to test further to determine cause, do not build 9616 at this time.
2012-03-14 added screenshot of wpf app
2012-03-15 Now supports Ice Cream Sandwhich Added option to options screen for one-click sending of old messages
2012-03-15 removed and ignored unneeded files
2012-03-15 Supports ICS themes Added option to options for one-click sending of old messages
2012-03-16 added image of updated .net controller
2012-03-22 added Resistor network (RN1) datasheet
2012-03-23 Changed UI to match closer to android (ICS) theme. Looks better overall
2012-03-23 removed debug folder from repo
2012-03-23 removed obj folder from repository
2012-03-23 scanned image of nearly built front (missing LEDs and 2 capacitors for now).
2012-04-10 Update Readme with current status update.
